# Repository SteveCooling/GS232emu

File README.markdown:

GS232emu
========

Copyright (c) 2012-2014 by LA1FTA Morten Johansen <morten@bzzt.no>

Description
-----------

Arduino code for antenna rotator logic. For use with H-bridges and a 3-phase motor driven as a stepper. Tries to emulate a Yaesu GS-232A controller.

Quality of emulation is not yet verified, but the command interface works. Supports rotation to specific azimuth, fetching current position and speed control.

Lacks some work for supporting the commands related to elevation.

License
-------

This work is licensed under the Creative Commons Attribution-ShareAlike 3.0 Unported License. To view a copy of this license, visit http://creativecommons.org/licenses/by-sa/3.0/.

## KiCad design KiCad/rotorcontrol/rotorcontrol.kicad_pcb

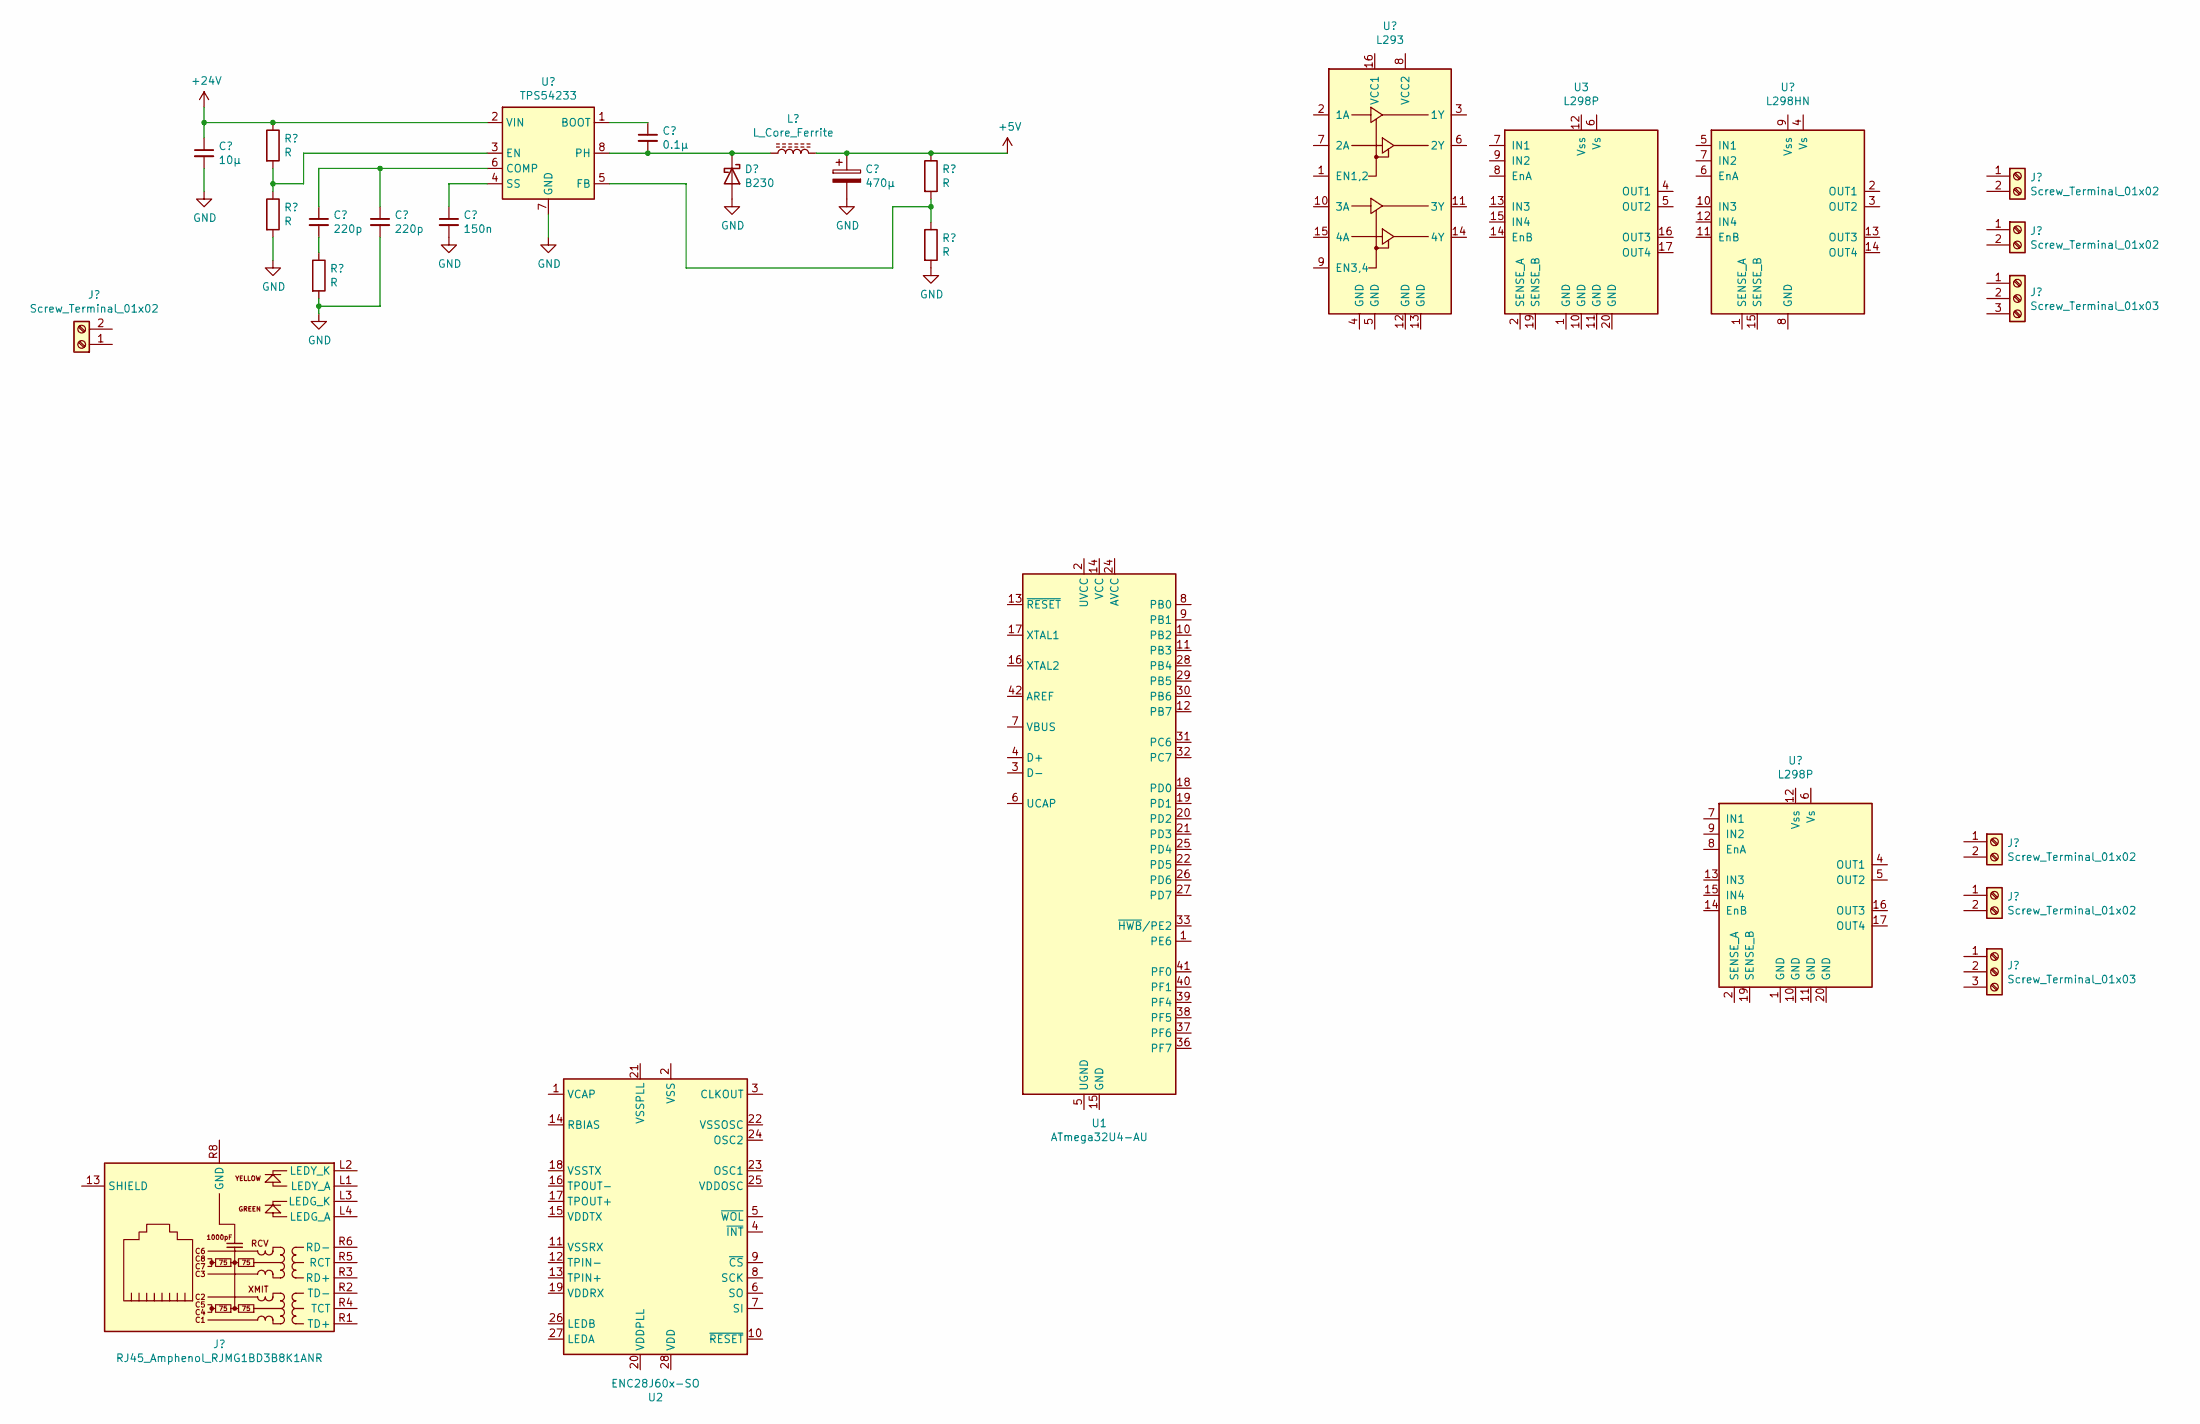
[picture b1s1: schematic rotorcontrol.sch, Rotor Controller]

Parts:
U1: ATmega32U4-AU; TQFP-44_10x10mm_P0.8mm
U2: ENC28J60x-SO; SOIC-28W_7.5x17.9mm_P1.27mm
U3: L298P; HSOP-20-1EP_11.0x15.9mm_P1.27mm_SlugDown_ThermalVias

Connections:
unnamed: U1.14 (VCC), U1.34 (VCC)
unnamed: U1.15 (GND), U1.23 (GND), U1.35 (GND), U1.43 (GND)
unnamed: U1.24 (AVCC), U1.44 (AVCC)

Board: 2 copper layers, 3 parts (0 on the bottom side), 3 nets, no tracks yet.

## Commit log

2012-07-19 First commit
    Timer, serial and a debug info function
2012-09-26 more work...
2012-09-26 added license information
2012-09-26 Markdown?
2014-03-01 PWM 3-phase synthesizing
2014-03-07 Motor driving works. Work on serial control interface and logic
2014-03-08 Serial interface logic work
2014-03-08 Speed control, calibration and cleanups
2014-03-08 Work on Hamlib compatibility
    I think OS X is messing with me. Need to test on Linux…
2014-03-08 Updated info
2014-03-10 Autospeed
    Speed mode X5 now gives a little more speed, plus automatic speed
    ramping on start and stop
2022-03-01 Migrated to PlatformIO and fixed a protocol bug
2022-03-01 Cleaned old files
2022-03-05 Motor control lib
2022-03-06 Picking some components
